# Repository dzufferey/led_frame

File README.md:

# led_frame

The backpanel for a "frame" with a bunch of RGB LEDs

## BoM

* [Teensy LC](https://www.pjrc.com/teensy/teensyLC.html)
* 90x [Addressable Through-Hole 5mm RGB LED, WS2811 Driver](https://www.pololu.com/product/2535)
* 8x THT resistors 100 Ohms
* 5V buck converter which can give at least 5A (like [this one](https://www.pololu.com/product/2851))
* barrel jack, switch, and screw terminal to connect to PSU
* ...

## Attributions

* The Kicad modules for Teensy-LC was adapted from the code at https://github.com/hedrickbt/teensy_breakout by Brooke Hedrick released under MIT License.
* LED lib from the kicad repo (https://kicad.github.io/symbols/LED, https://kicad.github.io/footprints/LED_THT, https://kicad.github.io/packages3d/LED_THT)

## License

The content of this project itself (excluding attributed parts) is licensed under the Creative Commons Attribution 3.0 license, and the source code in the `code` folder is licensed under the MIT license.

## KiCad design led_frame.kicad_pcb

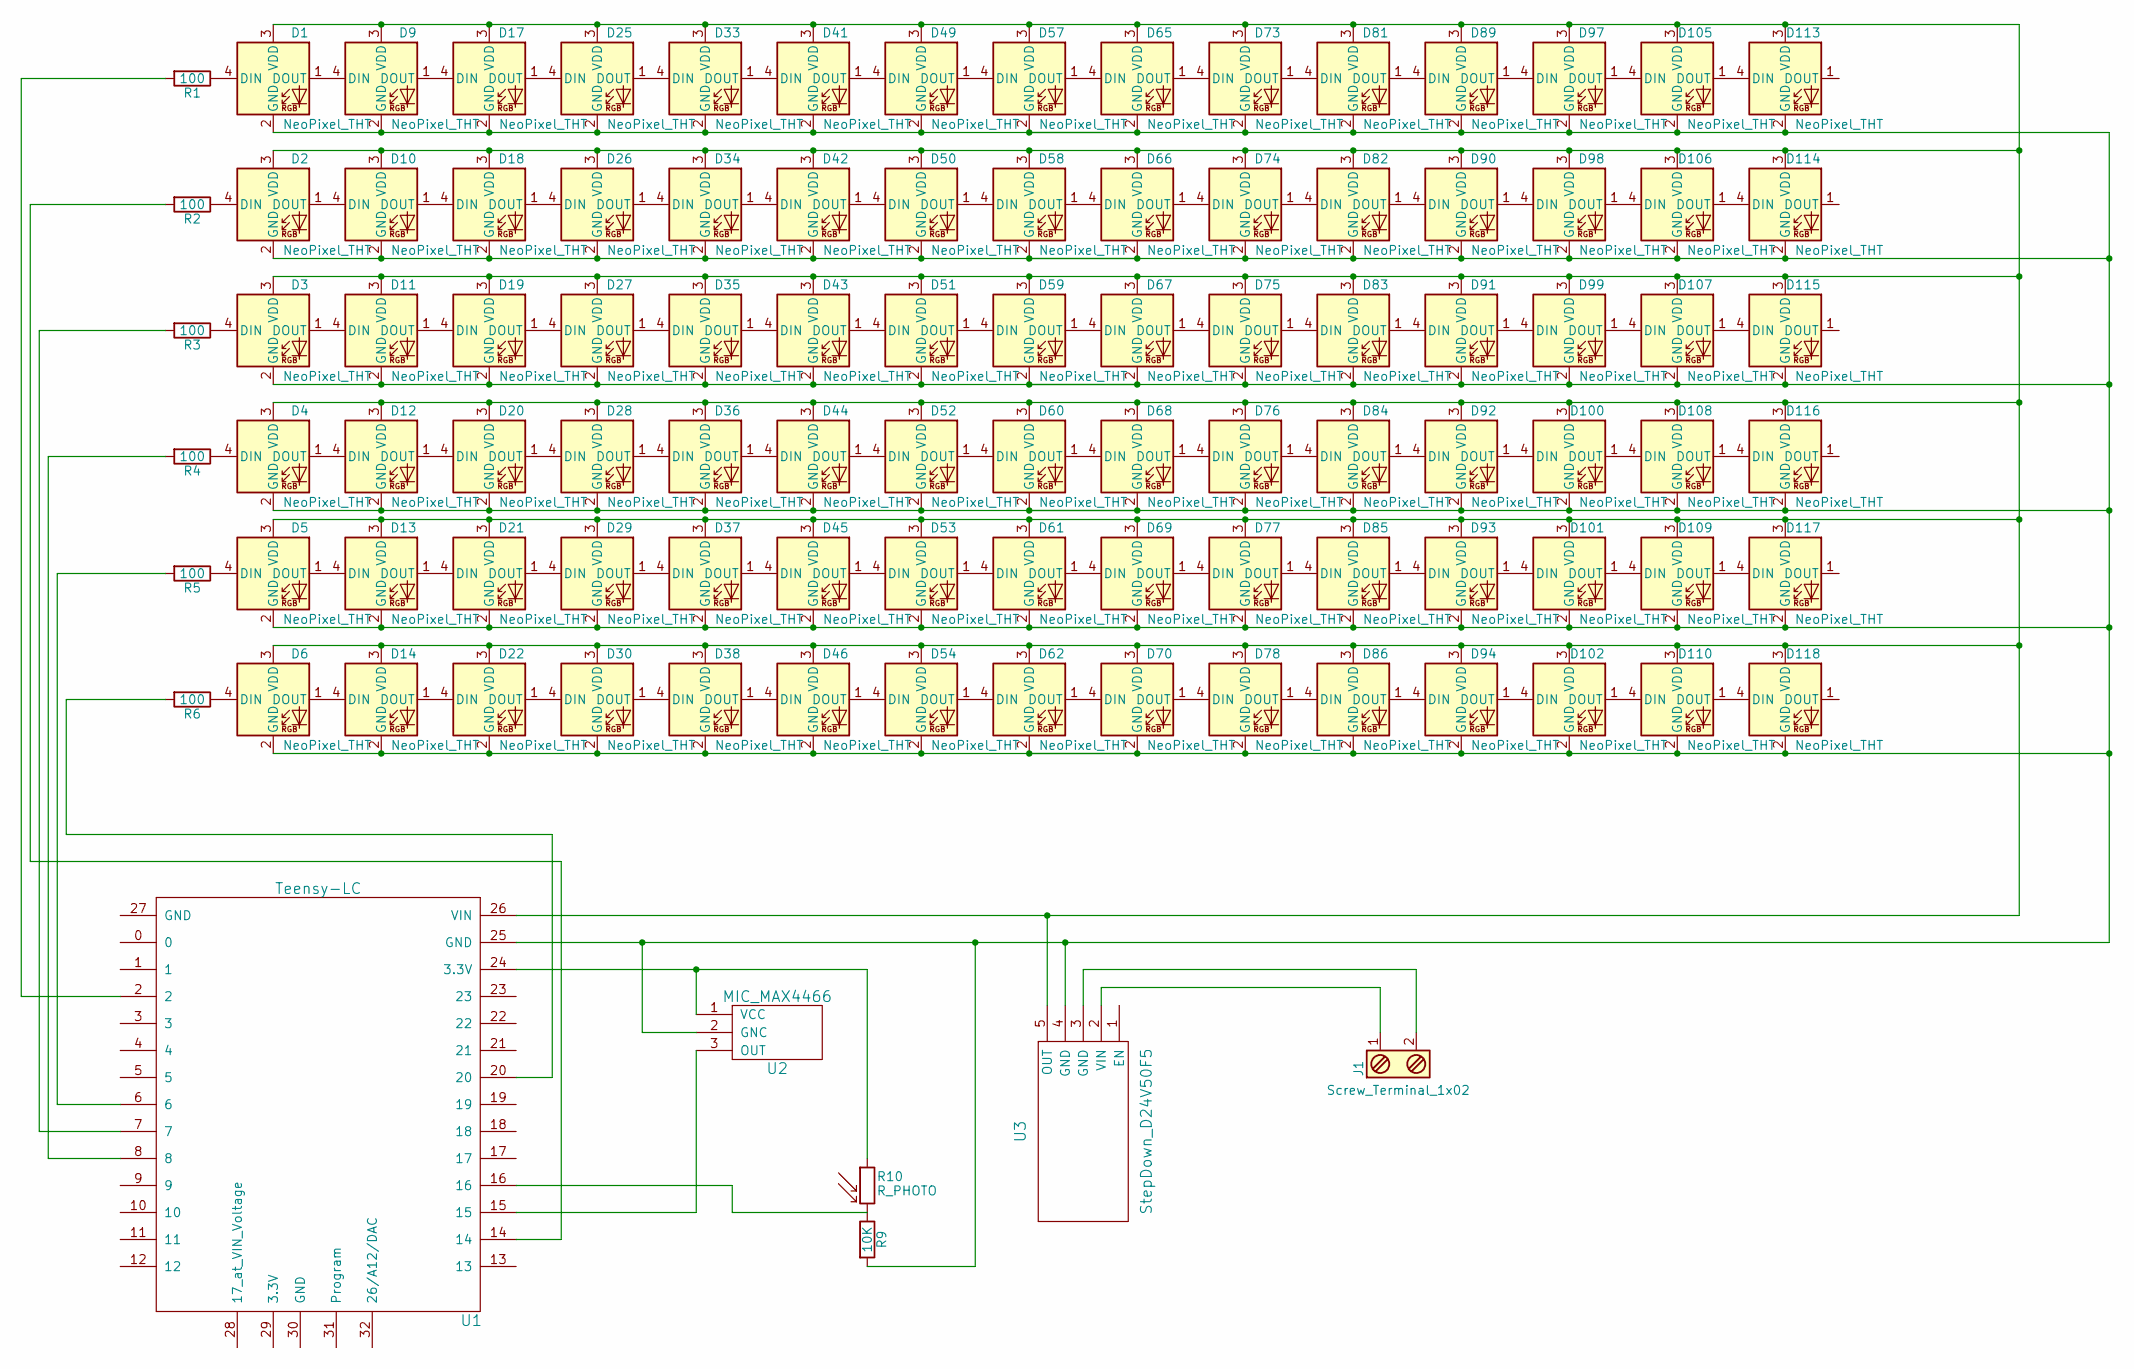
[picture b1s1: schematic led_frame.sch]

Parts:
D1, D2, D3, D4, D5, D6, D9, D10, D11, D12, D13, D14, D17, D18, D19, D20, D21, D22, D25, D26, D27, D28, D29, D30, D33, D34, D35, D36, D37, D38, D41, D42, D43, D44, D45, D46, D49, D50, D51, D52, D53, D54, D57, D58, D59, D60, D61, D62, D65, D66, D67, D68, D69, D70, D73, D74, D75, D76, D77, D78, D81, D82, D83, D84, D85, D86, D89, D90, D91, D92, D93, D94, D97, D98, D99, D100, D101, D102, D105, D106, D107, D108, D109, D110, D113, D114, D115, D116, D117, D118: NeoPixel_THT; LED_D5.0mm-4
J1: Screw_Terminal_1x02; TerminalBlock_Pheonix_PT-3.5mm_2pol
R1, R2, R3, R4, R5, R6: 100; R_Axial_DIN0207_L6.3mm_D2.5mm_P7.62mm_Horizontal
R9: 10K; R_Axial_DIN0207_L6.3mm_D2.5mm_P7.62mm_Horizontal
R10: R_PHOTO; R1
U1: Teensy-LC; teensy-lc
U2: MIC_MAX4466; MAX4466_adafruit
U3: StepDown_D24V50F5; D24V50F5_pololu

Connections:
unnamed: D1.1 (DOUT), D9.4 (DIN)
unnamed: D1.2 (GND), D2.2 (GND), D3.2 (GND), D4.2 (GND), D5.2 (GND), D6.2 (GND), D9.2 (GND), D10.2 (GND), D11.2 (GND), D12.2 (GND), D13.2 (GND), D14.2 (GND), D17.2 (GND), D18.2 (GND), D19.2 (GND), D20.2 (GND), D21.2 (GND), D22.2 (GND), D25.2 (GND), D26.2 (GND), D27.2 (GND), D28.2 (GND), D29.2 (GND), D30.2 (GND), D33.2 (GND), D34.2 (GND), D35.2 (GND), D36.2 (GND), D37.2 (GND), D38.2 (GND), D41.2 (GND), D42.2 (GND), D43.2 (GND), D44.2 (GND), D45.2 (GND), D46.2 (GND), D49.2 (GND), D50.2 (GND), D51.2 (GND), D52.2 (GND), D53.2 (GND), D54.2 (GND), D57.2 (GND), D58.2 (GND), D59.2 (GND), D60.2 (GND), D61.2 (GND), D62.2 (GND), D65.2 (GND), D66.2 (GND), D67.2 (GND), D68.2 (GND), D69.2 (GND), D70.2 (GND), D73.2 (GND), D74.2 (GND), D75.2 (GND), D76.2 (GND), D77.2 (GND), D78.2 (GND), D81.2 (GND), D82.2 (GND), D83.2 (GND), D84.2 (GND), D85.2 (GND), D86.2 (GND), D89.2 (GND), D90.2 (GND), D91.2 (GND), D92.2 (GND), D93.2 (GND), D94.2 (GND), D97.2 (GND), D98.2 (GND), D99.2 (GND), D100.2 (GND), D101.2 (GND), D102.2 (GND), D105.2 (GND), D106.2 (GND), D107.2 (GND), D108.2 (GND), D109.2 (GND), D110.2 (GND), D113.2 (GND), D114.2 (GND), D115.2 (GND), D116.2 (GND), D117.2 (GND), D118.2 (GND), R9.2, U1.25 (GND), U2.2 (GNC), U3.4 (GND)
unnamed: D1.3 (VDD), D2.3 (VDD), D3.3 (VDD), D4.3 (VDD), D5.3 (VDD), D6.3 (VDD), D9.3 (VDD), D10.3 (VDD), D11.3 (VDD), D12.3 (VDD), D13.3 (VDD), D14.3 (VDD), D17.3 (VDD), D18.3 (VDD), D19.3 (VDD), D20.3 (VDD), D21.3 (VDD), D22.3 (VDD), D25.3 (VDD), D26.3 (VDD), D27.3 (VDD), D28.3 (VDD), D29.3 (VDD), D30.3 (VDD), D33.3 (VDD), D34.3 (VDD), D35.3 (VDD), D36.3 (VDD), D37.3 (VDD), D38.3 (VDD), D41.3 (VDD), D42.3 (VDD), D43.3 (VDD), D44.3 (VDD), D45.3 (VDD), D46.3 (VDD), D49.3 (VDD), D50.3 (VDD), D51.3 (VDD), D52.3 (VDD), D53.3 (VDD), D54.3 (VDD), D57.3 (VDD), D58.3 (VDD), D59.3 (VDD), D60.3 (VDD), D61.3 (VDD), D62.3 (VDD), D65.3 (VDD), D66.3 (VDD), D67.3 (VDD), D68.3 (VDD), D69.3 (VDD), D70.3 (VDD), D73.3 (VDD), D74.3 (VDD), D75.3 (VDD), D76.3 (VDD), D77.3 (VDD), D78.3 (VDD), D81.3 (VDD), D82.3 (VDD), D83.3 (VDD), D84.3 (VDD), D85.3 (VDD), D86.3 (VDD), D89.3 (VDD), D90.3 (VDD), D91.3 (VDD), D92.3 (VDD), D93.3 (VDD), D94.3 (VDD), D97.3 (VDD), D98.3 (VDD), D99.3 (VDD), D100.3 (VDD), D101.3 (VDD), D102.3 (VDD), D105.3 (VDD), D106.3 (VDD), D107.3 (VDD), D108.3 (VDD), D109.3 (VDD), D110.3 (VDD), D113.3 (VDD), D114.3 (VDD), D115.3 (VDD), D116.3 (VDD), D117.3 (VDD), D118.3 (VDD), U1.26 (VIN), U3.5 (OUT)
unnamed: D1.4 (DIN), R1.1
unnamed: D2.4 (DIN), R2.1
unnamed: D3.4 (DIN), R3.1
unnamed: D4.4 (DIN), R4.1
unnamed: D5.4 (DIN), R5.1
unnamed: D6.4 (DIN), R6.1
unnamed: D10.1 (DOUT), D18.4 (DIN)
unnamed: D2.1 (DOUT), D10.4 (DIN)
unnamed: D11.1 (DOUT), D19.4 (DIN)
unnamed: D3.1 (DOUT), D11.4 (DIN)
unnamed: D12.1 (DOUT), D20.4 (DIN)
unnamed: D4.1 (DOUT), D12.4 (DIN)
unnamed: D13.1 (DOUT), D21.4 (DIN)
unnamed: D5.1 (DOUT), D13.4 (DIN)
unnamed: D14.1 (DOUT), D22.4 (DIN)
unnamed: D6.1 (DOUT), D14.4 (DIN)
unnamed: D17.1 (DOUT), D25.4 (DIN)
unnamed: D9.1 (DOUT), D17.4 (DIN)
unnamed: D18.1 (DOUT), D26.4 (DIN)
unnamed: D19.1 (DOUT), D27.4 (DIN)
unnamed: D20.1 (DOUT), D28.4 (DIN)
unnamed: D21.1 (DOUT), D29.4 (DIN)
unnamed: D22.1 (DOUT), D30.4 (DIN)
unnamed: D25.1 (DOUT), D33.4 (DIN)
unnamed: D26.1 (DOUT), D34.4 (DIN)
unnamed: D27.1 (DOUT), D35.4 (DIN)
unnamed: D28.1 (DOUT), D36.4 (DIN)
unnamed: D29.1 (DOUT), D37.4 (DIN)
unnamed: D30.1 (DOUT), D38.4 (DIN)
unnamed: D33.1 (DOUT), D41.4 (DIN)
unnamed: D34.1 (DOUT), D42.4 (DIN)
unnamed: D35.1 (DOUT), D43.4 (DIN)
unnamed: D36.1 (DOUT), D44.4 (DIN)
unnamed: D37.1 (DOUT), D45.4 (DIN)
unnamed: D38.1 (DOUT), D46.4 (DIN)
unnamed: D41.1 (DOUT), D49.4 (DIN)
unnamed: D42.1 (DOUT), D50.4 (DIN)
unnamed: D43.1 (DOUT), D51.4 (DIN)
unnamed: D44.1 (DOUT), D52.4 (DIN)
unnamed: D45.1 (DOUT), D53.4 (DIN)
unnamed: D46.1 (DOUT), D54.4 (DIN)
unnamed: D49.1 (DOUT), D57.4 (DIN)
unnamed: D50.1 (DOUT), D58.4 (DIN)
unnamed: D51.1 (DOUT), D59.4 (DIN)
unnamed: D52.1 (DOUT), D60.4 (DIN)
unnamed: D53.1 (DOUT), D61.4 (DIN)
unnamed: D54.1 (DOUT), D62.4 (DIN)
unnamed: D57.1 (DOUT), D65.4 (DIN)
unnamed: D58.1 (DOUT), D66.4 (DIN)
unnamed: D59.1 (DOUT), D67.4 (DIN)
unnamed: D60.1 (DOUT), D68.4 (DIN)
unnamed: D61.1 (DOUT), D69.4 (DIN)
unnamed: D62.1 (DOUT), D70.4 (DIN)
unnamed: D65.1 (DOUT), D73.4 (DIN)
unnamed: D66.1 (DOUT), D74.4 (DIN)
unnamed: D67.1 (DOUT), D75.4 (DIN)
unnamed: D68.1 (DOUT), D76.4 (DIN)
unnamed: D69.1 (DOUT), D77.4 (DIN)
unnamed: D70.1 (DOUT), D78.4 (DIN)
unnamed: D73.1 (DOUT), D81.4 (DIN)
unnamed: D74.1 (DOUT), D82.4 (DIN)
unnamed: D75.1 (DOUT), D83.4 (DIN)
unnamed: D76.1 (DOUT), D84.4 (DIN)
unnamed: D77.1 (DOUT), D85.4 (DIN)
unnamed: D78.1 (DOUT), D86.4 (DIN)
unnamed: D81.1 (DOUT), D89.4 (DIN)
unnamed: D82.1 (DOUT), D90.4 (DIN)
unnamed: D83.1 (DOUT), D91.4 (DIN)
unnamed: D84.1 (DOUT), D92.4 (DIN)
unnamed: D85.1 (DOUT), D93.4 (DIN)
unnamed: D86.1 (DOUT), D94.4 (DIN)
unnamed: D89.1 (DOUT), D97.4 (DIN)
unnamed: D90.1 (DOUT), D98.4 (DIN)
unnamed: D91.1 (DOUT), D99.4 (DIN)
unnamed: D100.1 (DOUT), D108.4 (DIN)
unnamed: D92.1 (DOUT), D100.4 (DIN)
unnamed: D101.1 (DOUT), D109.4 (DIN)
unnamed: D93.1 (DOUT), D101.4 (DIN)
unnamed: D102.1 (DOUT), D110.4 (DIN)
unnamed: D94.1 (DOUT), D102.4 (DIN)
unnamed: D105.1 (DOUT), D113.4 (DIN)
unnamed: D97.1 (DOUT), D105.4 (DIN)
unnamed: D106.1 (DOUT), D114.4 (DIN)
unnamed: D98.1 (DOUT), D106.4 (DIN)
unnamed: D107.1 (DOUT), D115.4 (DIN)
unnamed: D99.1 (DOUT), D107.4 (DIN)
unnamed: D108.1 (DOUT), D116.4 (DIN)
unnamed: D109.1 (DOUT), D117.4 (DIN)
unnamed: D110.1 (DOUT), D118.4 (DIN)
unnamed: J1.1, U3.2 (VIN)
unnamed: J1.2, U3.3 (GND)
unnamed: R1.2, U1.2
unnamed: R2.2, U1.14
unnamed: R3.2, U1.7
unnamed: R4.2, U1.8
unnamed: R5.2, U1.6
unnamed: R6.2, U1.20
unnamed: R10.1, U1.24 (3.3V), U2.1 (VCC)
unnamed: R9.1, R10.2, U1.16
unnamed: U1.15, U2.3 (OUT)

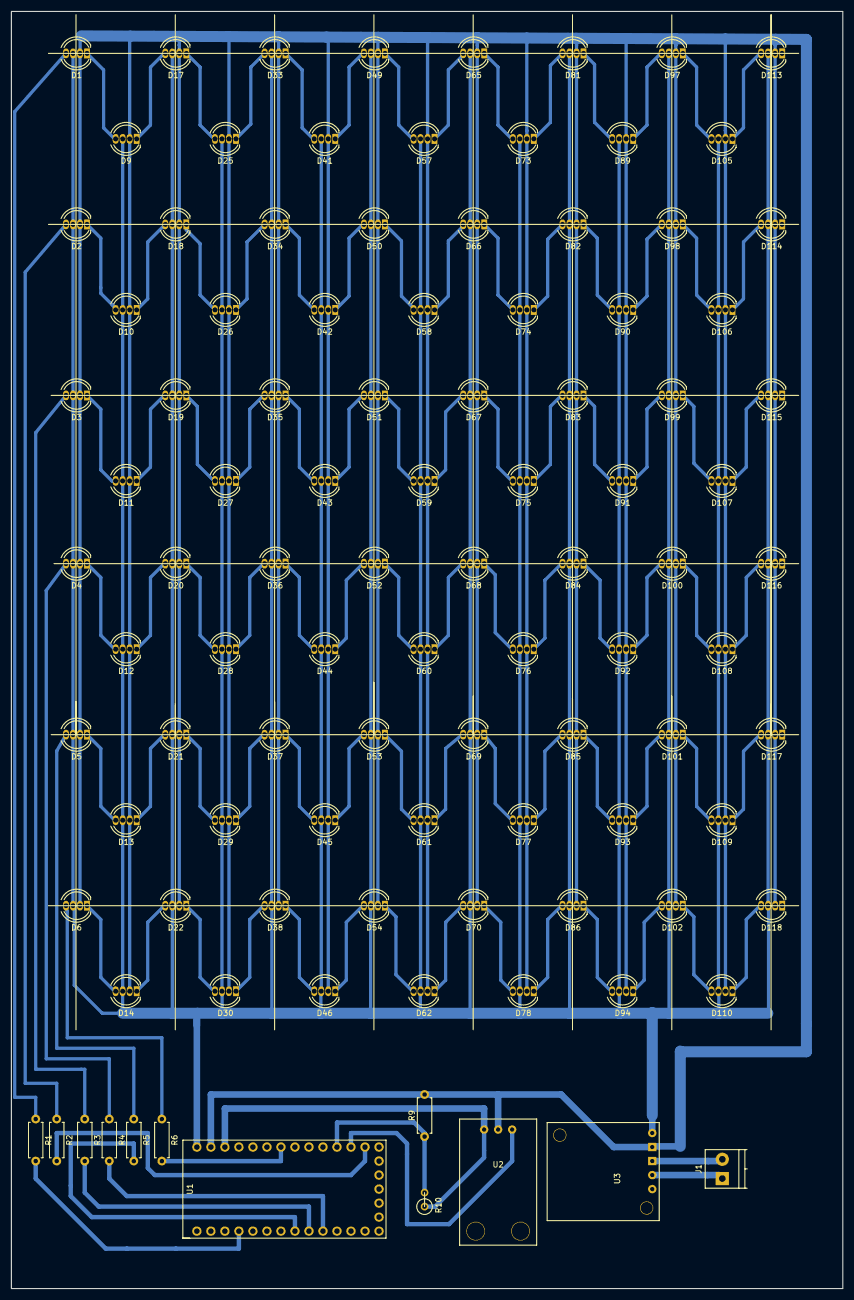
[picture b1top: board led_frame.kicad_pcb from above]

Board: 2 copper layers, 150.7 x 231.5 mm, 102 parts (0 on the bottom side), 103 nets.

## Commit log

2018-03-19 working ...
2018-04-28 layout
2018-05-03 fixing some connections
2018-05-05 minor
